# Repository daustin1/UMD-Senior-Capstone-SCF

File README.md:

# ece457SCF
Short Circuit Finder Senior Design Project

Team Lead: Matt Duncan;
Team Members: David Austin,
Mike Dugas

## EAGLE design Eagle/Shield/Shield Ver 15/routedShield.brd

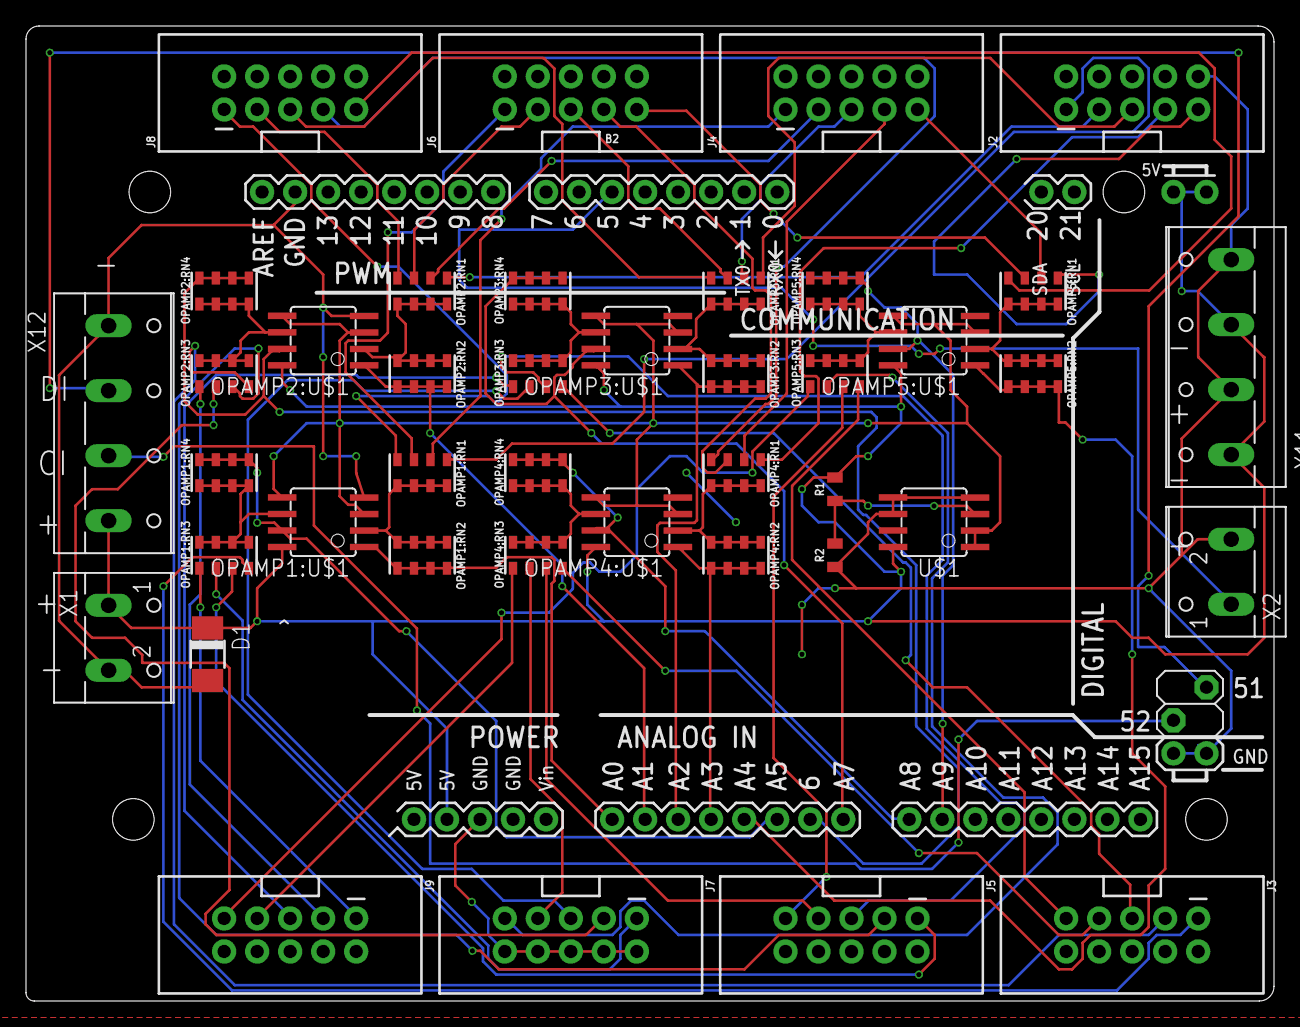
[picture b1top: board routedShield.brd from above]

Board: 2 copper layers, 96.0 x 75.0 mm, 42 parts (0 on the bottom side), 67 nets.

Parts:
B2: ARDUINO_MEGA_R3_EDITARDUINO_MEGA_EDIT; ARDUINO_MEGA_EDIT
D1: DO-214AC
J2, J3, J4, J5, J6, J7, J8, J9: AVR_SPI_PROG_5X2_NEWPTH2; 2X5-SHROUDED
OPAMP1:RN1, OPAMP1:RN2, OPAMP1:RN3, OPAMP1:RN4, OPAMP2:RN1, OPAMP2:RN2, OPAMP2:RN3, OPAMP2:RN4, OPAMP3:RN1, OPAMP3:RN2, OPAMP3:RN3, OPAMP3:RN4, OPAMP4:RN1, OPAMP4:RN2, OPAMP4:RN3, OPAMP4:RN4, OPAMP5:RN1, OPAMP5:RN2, OPAMP5:RN3, OPAMP5:RN4: 10k; 0805-ARV_EDIT10K
OPAMP1:U$1, OPAMP2:U$1, OPAMP3:U$1, OPAMP4:U$1, OPAMP5:U$1: MCP6002SMT; SOIC8
R1, R2: 1k; 0805
U$1: MCP6002SMT; SOIC8
X1, X2: W237-102
X11, X12: W237-4

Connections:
+5V: B2.5V@0, B2.5V@1, B2.5V@2, D1.C, OPAMP1:U$1.8, OPAMP2:U$1.8, OPAMP3:U$1.8, OPAMP4:U$1.8, OPAMP5:U$1.8, R1.2, U$1.8, X1.1, X11.1, X11.3, X12.4
A1O: B2.A0, OPAMP1:RN2.5, OPAMP1:RN2.6, OPAMP1:RN2.7, OPAMP1:RN2.8, OPAMP1:U$1.1
A2O: B2.A1, OPAMP2:RN2.5, OPAMP2:RN2.6, OPAMP2:RN2.7, OPAMP2:RN2.8, OPAMP2:U$1.1
A3O: B2.A2, OPAMP3:RN2.5, OPAMP3:RN2.6, OPAMP3:RN2.7, OPAMP3:RN2.8, OPAMP3:U$1.1
A4O: B2.A3, OPAMP4:RN2.5, OPAMP4:RN2.6, OPAMP4:RN2.7, OPAMP4:RN2.8, OPAMP4:U$1.1
A5O: B2.A4, OPAMP5:RN2.5, OPAMP5:RN2.6, OPAMP5:RN2.7, OPAMP5:RN2.8, OPAMP5:U$1.1
A6O: B2.A5, OPAMP1:RN4.5, OPAMP1:RN4.6, OPAMP1:RN4.7, OPAMP1:RN4.8, OPAMP1:U$1.7
A7O: B2.A6, OPAMP2:RN4.5, OPAMP2:RN4.6, OPAMP2:RN4.7, OPAMP2:RN4.8, OPAMP2:U$1.7
A8O: B2.A7, OPAMP3:RN4.5, OPAMP3:RN4.6, OPAMP3:RN4.7, OPAMP3:RN4.8, OPAMP3:U$1.7
A9O: B2.A8, OPAMP4:RN4.5, OPAMP4:RN4.6, OPAMP4:RN4.7, OPAMP4:RN4.8, OPAMP4:U$1.7
A10O: B2.A9, OPAMP5:RN4.5, OPAMP5:RN4.6, OPAMP5:RN4.7, OPAMP5:RN4.8, OPAMP5:U$1.7
CI: B2.52, X12.3
DI: B2.51, X12.2
GND: B2.GND@0, B2.GND@1, B2.GND@2, B2.GND@3, B2.GND@4, D1.A, J2.2, J2.4, J2.6, J2.8, J2.10, J3.2, J3.4, J3.6, J3.8, J3.10, J4.2, J4.4, J4.6, J4.8, J4.10, J5.2, J5.4, J5.6, J5.8, J5.10, J6.2, J6.4, J6.6, J6.8, J6.10, J7.2, J7.4, J7.6, J7.8, J7.10, J8.2, J8.4, J8.6, J8.8, J8.10, J9.2, J9.4, J9.6, J9.8, J9.10, OPAMP1:U$1.4, OPAMP2:U$1.4, OPAMP3:U$1.4, OPAMP4:U$1.4, OPAMP5:U$1.4, R2.1, U$1.4, U$1.5, U$1.6, X1.2, X2.2, X11.2, X11.4, X12.1
unnamed: R1.1, R2.2, U$1.3
OPAMP1:N$1: OPAMP1:RN3.5, OPAMP1:RN3.6, OPAMP1:RN3.7, OPAMP1:RN3.8, OPAMP1:RN4.1, OPAMP1:RN4.2, OPAMP1:RN4.3, OPAMP1:RN4.4, OPAMP1:U$1.6
OPAMP1:N$2: OPAMP1:RN1.5, OPAMP1:RN1.6, OPAMP1:RN1.7, OPAMP1:RN1.8, OPAMP1:RN2.1, OPAMP1:RN2.2, OPAMP1:RN2.3, OPAMP1:RN2.4, OPAMP1:U$1.2
OPAMP2:N$1: OPAMP2:RN3.5, OPAMP2:RN3.6, OPAMP2:RN3.7, OPAMP2:RN3.8, OPAMP2:RN4.1, OPAMP2:RN4.2, OPAMP2:RN4.3, OPAMP2:RN4.4, OPAMP2:U$1.6
OPAMP2:N$2: OPAMP2:RN1.5, OPAMP2:RN1.6, OPAMP2:RN1.7, OPAMP2:RN1.8, OPAMP2:RN2.1, OPAMP2:RN2.2, OPAMP2:RN2.3, OPAMP2:RN2.4, OPAMP2:U$1.2
OPAMP3:N$1: OPAMP3:RN3.5, OPAMP3:RN3.6, OPAMP3:RN3.7, OPAMP3:RN3.8, OPAMP3:RN4.1, OPAMP3:RN4.2, OPAMP3:RN4.3, OPAMP3:RN4.4, OPAMP3:U$1.6
OPAMP3:N$2: OPAMP3:RN1.5, OPAMP3:RN1.6, OPAMP3:RN1.7, OPAMP3:RN1.8, OPAMP3:RN2.1, OPAMP3:RN2.2, OPAMP3:RN2.3, OPAMP3:RN2.4, OPAMP3:U$1.2
OPAMP4:N$1: OPAMP4:RN3.5, OPAMP4:RN3.6, OPAMP4:RN3.7, OPAMP4:RN3.8, OPAMP4:RN4.1, OPAMP4:RN4.2, OPAMP4:RN4.3, OPAMP4:RN4.4, OPAMP4:U$1.6
OPAMP4:N$2: OPAMP4:RN1.5, OPAMP4:RN1.6, OPAMP4:RN1.7, OPAMP4:RN1.8, OPAMP4:RN2.1, OPAMP4:RN2.2, OPAMP4:RN2.3, OPAMP4:RN2.4, OPAMP4:U$1.2
OPAMP5:N$1: OPAMP5:RN3.5, OPAMP5:RN3.6, OPAMP5:RN3.7, OPAMP5:RN3.8, OPAMP5:RN4.1, OPAMP5:RN4.2, OPAMP5:RN4.3, OPAMP5:RN4.4, OPAMP5:U$1.6
OPAMP5:N$2: OPAMP5:RN1.5, OPAMP5:RN1.6, OPAMP5:RN1.7, OPAMP5:RN1.8, OPAMP5:RN2.1, OPAMP5:RN2.2, OPAMP5:RN2.3, OPAMP5:RN2.4, OPAMP5:U$1.2
S1A: J2.1, OPAMP1:RN1.1
S1B: J3.1, OPAMP1:RN3.4
S2A: J2.3, OPAMP2:RN1.1
S2B: J3.3, OPAMP2:RN3.4
S3A: J2.5, OPAMP3:RN1.1
S3B: J3.5, OPAMP3:RN3.4
S4A: J2.7, OPAMP4:RN1.1
S4B: J3.7, OPAMP4:RN3.4
S5A: J2.9, OPAMP5:RN1.1
S5B: J3.9, OPAMP5:RN3.4
S6A: J4.1, OPAMP1:RN1.2
S6B: J5.1, OPAMP1:RN3.3
S7A: J4.3, OPAMP2:RN1.2
S7B: J5.3, OPAMP2:RN3.3
S8A: J4.5, OPAMP3:RN1.2
S8B: J5.5, OPAMP3:RN3.3
S9A: J4.7, OPAMP4:RN1.2
S9B: J5.7, OPAMP4:RN3.3
S10A: J4.9, OPAMP5:RN1.2
S10B: J5.9, OPAMP5:RN3.3
S11A: J6.1, OPAMP1:RN1.3
S11B: J7.1, OPAMP1:RN3.2
S12A: J6.3, OPAMP2:RN1.3
S12B: J7.3, OPAMP2:RN3.2
S13A: J6.5, OPAMP3:RN1.3
S13B: J7.5, OPAMP3:RN3.2
S14A: J6.7, OPAMP4:RN1.3
S14B: J7.7, OPAMP4:RN3.2
S15A: J6.9, OPAMP5:RN1.3
S15B: J7.9, OPAMP5:RN3.2
S16A: J8.1, OPAMP1:RN1.4
S16B: J9.1, OPAMP1:RN3.1
S17A: J8.3, OPAMP2:RN1.4
S17B: J9.3, OPAMP2:RN3.1
S18A: J8.5, OPAMP3:RN1.4
S18B: J9.5, OPAMP3:RN3.1
S19A: J8.7, OPAMP4:RN1.4
S19B: J9.7, OPAMP4:RN3.1
S20A: J8.9, OPAMP5:RN1.4
S20B: J9.9, OPAMP5:RN3.1
TTL: B2.5, X2.1
VREF: OPAMP1:U$1.3, OPAMP1:U$1.5, OPAMP2:U$1.3, OPAMP2:U$1.5, OPAMP3:U$1.3, OPAMP3:U$1.5, OPAMP4:U$1.3, OPAMP4:U$1.5, OPAMP5:U$1.3, OPAMP5:U$1.5, U$1.1, U$1.2

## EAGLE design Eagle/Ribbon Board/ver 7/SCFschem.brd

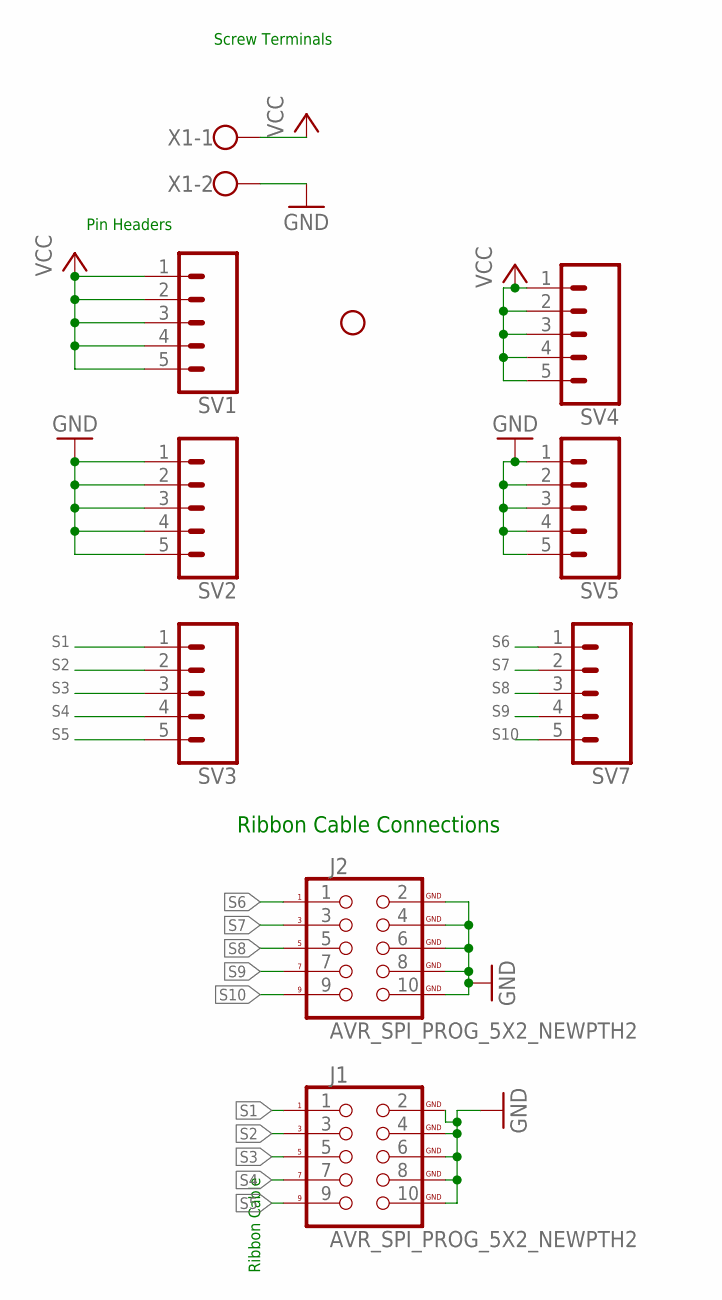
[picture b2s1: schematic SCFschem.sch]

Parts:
H1: STAND-OFF
J1, J2: AVR_SPI_PROG_5X2_NEWPTH2; 2X5-SHROUDED
SV1, SV2, SV3, SV4, SV5, SV7: CONN_05; 1X05
X1: 1X02_5MM_SCREW; W237-102

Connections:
GND: J1.2 (GND), J1.4 (GND), J1.6 (GND), J1.8 (GND), J1.10 (GND), J2.2 (GND), J2.4 (GND), J2.6 (GND), J2.8 (GND), J2.10 (GND), SV2.1, SV2.2, SV2.3, SV2.4, SV2.5, SV5.1, SV5.2, SV5.3, SV5.4, SV5.5, X1.2
S1: J1.1, SV3.1
S2: J1.3, SV3.2
S3: J1.5, SV3.3
S4: J1.7, SV3.4
S5: J1.9, SV3.5
S6: J2.1, SV7.1
S7: J2.3, SV7.2
S8: J2.5, SV7.3
S9: J2.7, SV7.4
S10: J2.9, SV7.5
VCC: SV1.1, SV1.2, SV1.3, SV1.4, SV1.5, SV4.1, SV4.2, SV4.3, SV4.4, SV4.5, X1.1

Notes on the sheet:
Screw Terminals
Ribbon Cable
Pin Headers
Ribbon Cable Connections

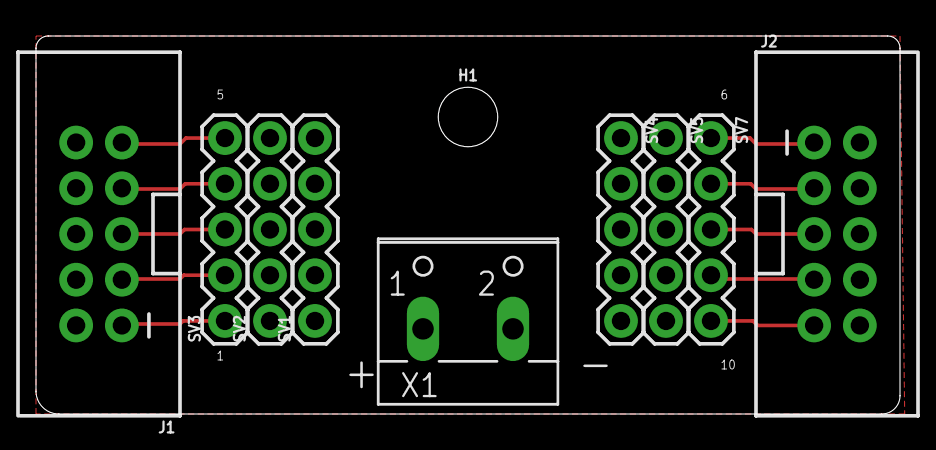
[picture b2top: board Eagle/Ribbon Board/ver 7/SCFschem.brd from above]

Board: 2 copper layers, 48.0 x 21.0 mm, 10 parts (0 on the bottom side), 12 nets.

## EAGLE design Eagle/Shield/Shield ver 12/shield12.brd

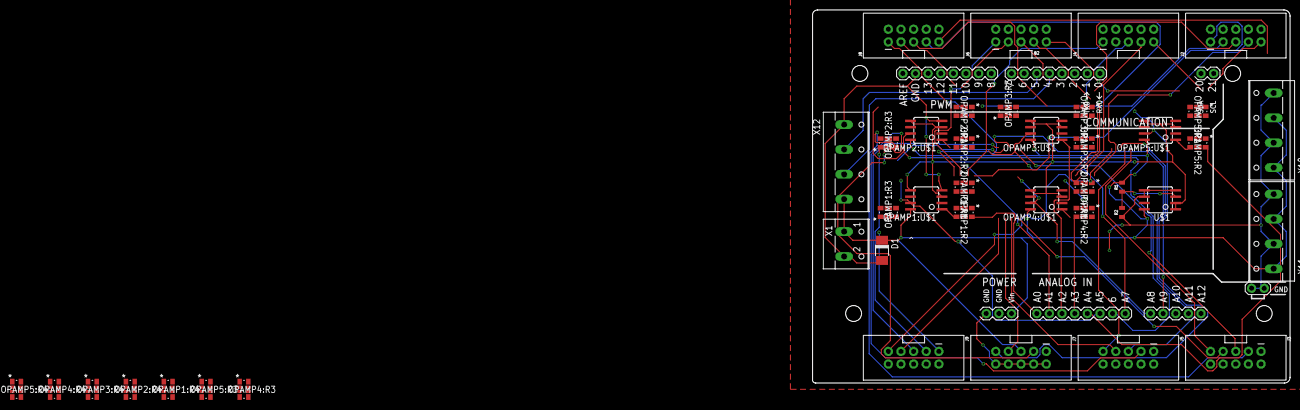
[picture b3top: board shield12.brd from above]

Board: 2 copper layers, 96.0 x 75.0 mm, 42 parts (0 on the bottom side), 46 nets.

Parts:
B2: ARDUINO_MEGA_R3_EDIT; ARDUINO_MEGA_EDIT
D1: DO-214AC
J2, J3, J4, J5, J6, J7, J8, J9: AVR_SPI_PROG_5X2_NEWPTH2; 2X5-SHROUDED
OPAMP1:R1, OPAMP1:R2, OPAMP1:R3, OPAMP1:R4, OPAMP2:R1, OPAMP2:R2, OPAMP2:R3, OPAMP2:R4, OPAMP3:R1, OPAMP3:R2, OPAMP3:R3, OPAMP3:R4, OPAMP4:R1, OPAMP4:R2, OPAMP4:R3, OPAMP4:R4, OPAMP5:R1, OPAMP5:R2, OPAMP5:R3, OPAMP5:R4: YC164-JR-0710KL; YAG_YC164
OPAMP1:U$1, OPAMP2:U$1, OPAMP3:U$1, OPAMP4:U$1, OPAMP5:U$1: MCP6002SMT; SOIC8
R1, R2: 1k; 0805
U$1: MCP6002SMT; SOIC8
X1: W237-102
X10, X11, X12: W237-4

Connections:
+5V: B2.VIN, D1.C, OPAMP1:U$1.8, OPAMP2:U$1.8, OPAMP3:U$1.8, OPAMP4:U$1.8, OPAMP5:U$1.8, R1.2, U$1.8, X1.1, X10.1, X10.3, X11.1, X11.3, X12.4
A1O: B2.A0, OPAMP1:R2.5, OPAMP1:R2.6, OPAMP1:R2.7, OPAMP1:R2.8, OPAMP1:U$1.1
A2O: B2.A1, OPAMP2:R2.5, OPAMP2:R2.6, OPAMP2:R2.7, OPAMP2:R2.8, OPAMP2:U$1.1
A3O: B2.A2, OPAMP3:R2.5, OPAMP3:R2.6, OPAMP3:R2.7, OPAMP3:R2.8, OPAMP3:U$1.1
A4O: B2.A3, OPAMP4:R2.5, OPAMP4:R2.6, OPAMP4:R2.7, OPAMP4:R2.8, OPAMP4:U$1.1
A5O: B2.A4, OPAMP5:R2.5, OPAMP5:R2.6, OPAMP5:R2.7, OPAMP5:R2.8, OPAMP5:U$1.1
A6O: B2.A5, OPAMP1:R4.5, OPAMP1:R4.6, OPAMP1:R4.7, OPAMP1:R4.8, OPAMP1:U$1.7
A7O: B2.A6, OPAMP2:R4.5, OPAMP2:R4.6, OPAMP2:R4.7, OPAMP2:R4.8, OPAMP2:U$1.7
A8O: B2.A7, OPAMP3:R4.5, OPAMP3:R4.6, OPAMP3:R4.7, OPAMP3:R4.8, OPAMP3:U$1.7
A9O: B2.A8, OPAMP4:R4.5, OPAMP4:R4.6, OPAMP4:R4.7, OPAMP4:R4.8, OPAMP4:U$1.7
A10O: B2.A9, OPAMP5:R4.5, OPAMP5:R4.6, OPAMP5:R4.7, OPAMP5:R4.8, OPAMP5:U$1.7
CI: B2.4, X12.3
DI: B2.5, X12.2
GND: B2.GND@0, B2.GND@1, B2.GND@2, B2.GND@3, B2.GND@4, D1.A, J2.2, J2.4, J2.6, J2.8, J2.10, J3.2, J3.4, J3.6, J3.8, J3.10, J4.2, J4.4, J4.6, J4.8, J4.10, J5.2, J5.4, J5.6, J5.8, J5.10, J6.2, J6.4, J6.6, J6.8, J6.10, J7.2, J7.4, J7.6, J7.8, J7.10, J8.2, J8.4, J8.6, J8.8, J8.10, J9.2, J9.4, J9.6, J9.8, J9.10, OPAMP1:U$1.4, OPAMP2:U$1.4, OPAMP3:U$1.4, OPAMP4:U$1.4, OPAMP5:U$1.4, R2.1, U$1.4, U$1.5, U$1.6, X1.2, X10.2, X10.4, X11.2, X11.4, X12.1
unnamed: R1.1, R2.2, U$1.3
OPAMP1:N$1: OPAMP1:R3.5, OPAMP1:R3.6, OPAMP1:R3.7, OPAMP1:R3.8, OPAMP1:R4.1, OPAMP1:R4.2, OPAMP1:R4.3, OPAMP1:R4.4, OPAMP1:U$1.6
OPAMP1:N$2: OPAMP1:R1.5, OPAMP1:R1.6, OPAMP1:R1.7, OPAMP1:R1.8, OPAMP1:R2.1, OPAMP1:R2.2, OPAMP1:R2.3, OPAMP1:R2.4, OPAMP1:U$1.2
OPAMP2:N$1: OPAMP2:R3.5, OPAMP2:R3.6, OPAMP2:R3.7, OPAMP2:R3.8, OPAMP2:R4.1, OPAMP2:R4.2, OPAMP2:R4.3, OPAMP2:R4.4, OPAMP2:U$1.6
OPAMP2:N$2: OPAMP2:R1.5, OPAMP2:R1.6, OPAMP2:R1.7, OPAMP2:R1.8, OPAMP2:R2.1, OPAMP2:R2.2, OPAMP2:R2.3, OPAMP2:R2.4, OPAMP2:U$1.2
OPAMP3:N$1: OPAMP3:R3.5, OPAMP3:R3.6, OPAMP3:R3.7, OPAMP3:R3.8, OPAMP3:R4.1, OPAMP3:R4.2, OPAMP3:R4.3, OPAMP3:R4.4, OPAMP3:U$1.6
OPAMP3:N$2: OPAMP3:R1.5, OPAMP3:R1.6, OPAMP3:R1.7, OPAMP3:R1.8, OPAMP3:R2.1, OPAMP3:R2.2, OPAMP3:R2.3, OPAMP3:R2.4, OPAMP3:U$1.2
OPAMP4:N$1: OPAMP4:R3.5, OPAMP4:R3.6, OPAMP4:R3.7, OPAMP4:R3.8, OPAMP4:R4.1, OPAMP4:R4.2, OPAMP4:R4.3, OPAMP4:R4.4, OPAMP4:U$1.6
OPAMP4:N$2: OPAMP4:R1.5, OPAMP4:R1.6, OPAMP4:R1.7, OPAMP4:R1.8, OPAMP4:R2.1, OPAMP4:R2.2, OPAMP4:R2.3, OPAMP4:R2.4, OPAMP4:U$1.2
OPAMP5:N$1: OPAMP5:R3.5, OPAMP5:R3.6, OPAMP5:R3.7, OPAMP5:R3.8, OPAMP5:R4.1, OPAMP5:R4.2, OPAMP5:R4.3, OPAMP5:R4.4, OPAMP5:U$1.6
OPAMP5:N$2: OPAMP5:R1.5, OPAMP5:R1.6, OPAMP5:R1.7, OPAMP5:R1.8, OPAMP5:R2.1, OPAMP5:R2.2, OPAMP5:R2.3, OPAMP5:R2.4, OPAMP5:U$1.2
S1B: J3.1, OPAMP1:R3.1
S2B: J3.3, OPAMP2:R3.1
S3B: J3.5, OPAMP3:R3.1
S4B: J3.7, OPAMP4:R3.1
S5B: J3.9, OPAMP5:R3.1
S6B: J5.1, OPAMP1:R3.2
S7B: J5.3, OPAMP2:R3.2
S8B: J5.5, OPAMP3:R3.2
S9B: J5.7, OPAMP4:R3.2
S10B: J5.9, OPAMP5:R3.2
S11B: J7.1, OPAMP1:R3.3
S12B: J7.3, OPAMP2:R3.3
S13B: J7.5, OPAMP3:R3.3
S14B: J7.7, OPAMP4:R3.3
S15B: J7.9, OPAMP5:R3.3
S16B: J9.1, OPAMP1:R3.4
S17B: J9.3, OPAMP2:R3.4
S18B: J9.5, OPAMP3:R3.4
S19B: J9.7, OPAMP4:R3.4
S20B: J9.9, OPAMP5:R3.4
VREF: OPAMP1:U$1.3, OPAMP1:U$1.5, OPAMP2:U$1.3, OPAMP2:U$1.5, OPAMP3:U$1.3, OPAMP3:U$1.5, OPAMP4:U$1.3, OPAMP4:U$1.5, OPAMP5:U$1.3, OPAMP5:U$1.5, U$1.1, U$1.2

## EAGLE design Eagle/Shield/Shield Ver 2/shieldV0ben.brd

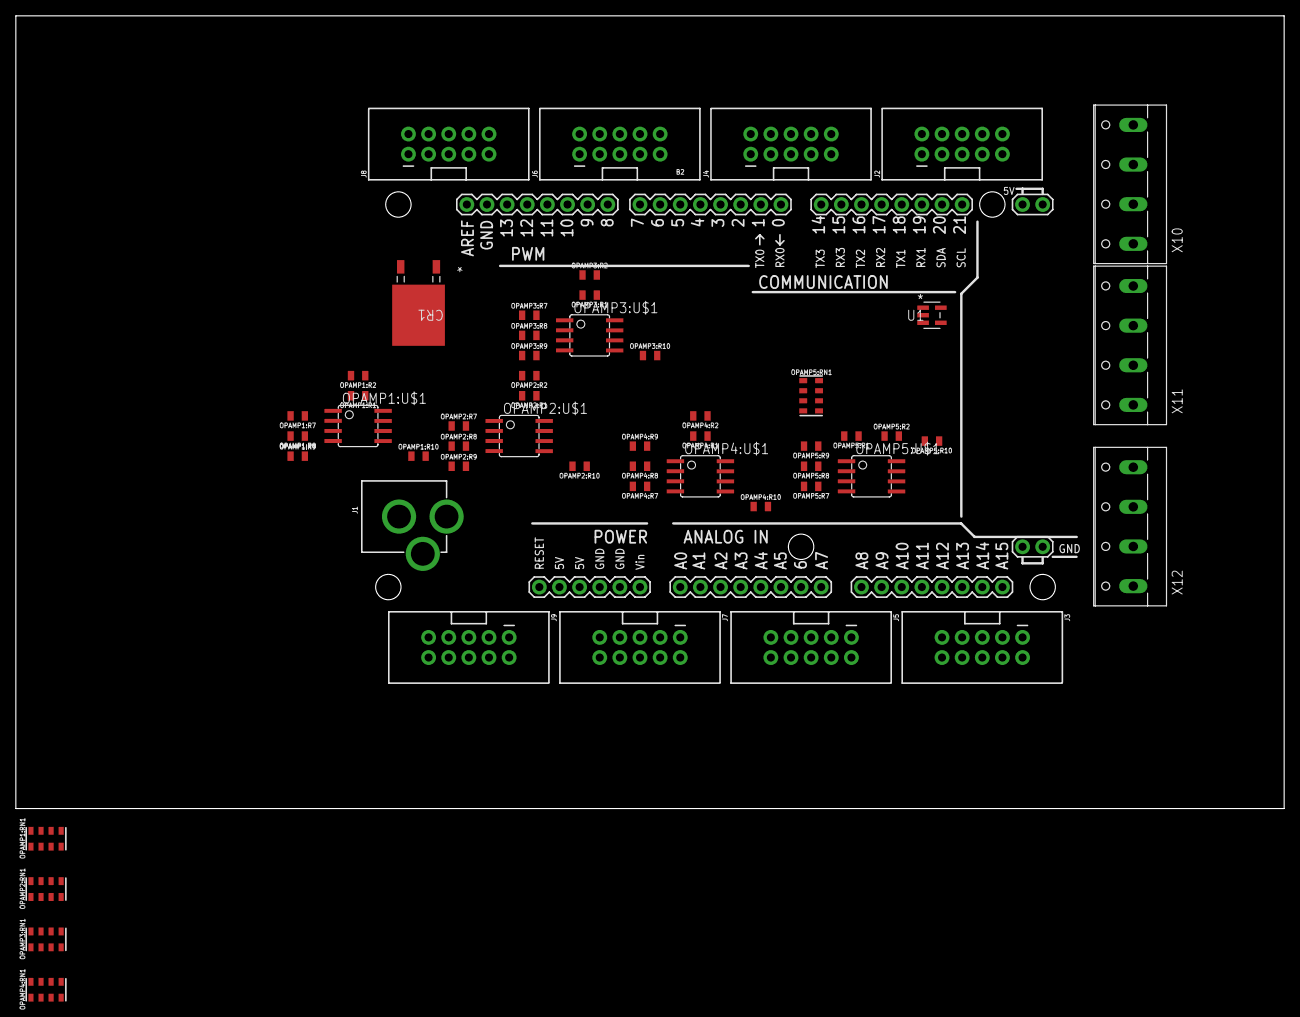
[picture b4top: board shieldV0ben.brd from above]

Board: 2 copper layers, 160.0 x 100.0 mm, 55 parts (0 on the bottom side), 62 nets, no tracks yet.

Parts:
B2: ARDUINO_MEGA_R3_EDIT; ARDUINO_MEGA_EDIT
CR1: L7805CDT-TR; DPAK
J1: POWER_JACK; POWER_JACK_PTH
J2, J3, J4, J5, J6, J7, J8, J9: AVR_SPI_PROG_5X2_NEWPTH2; 2X5-SHROUDED
OPAMP1:R1, OPAMP1:R2, OPAMP2:R1, OPAMP2:R2, OPAMP3:R1, OPAMP3:R2, OPAMP4:R1, OPAMP4:R2, OPAMP5:R1, OPAMP5:R2: 1k; 0805
OPAMP1:R7, OPAMP1:R8, OPAMP1:R9, OPAMP1:R10, OPAMP2:R7, OPAMP2:R8, OPAMP2:R9, OPAMP2:R10, OPAMP3:R7, OPAMP3:R8, OPAMP3:R9, OPAMP3:R10, OPAMP4:R7, OPAMP4:R8, OPAMP4:R9, OPAMP4:R10, OPAMP5:R7, OPAMP5:R8, OPAMP5:R9, OPAMP5:R10: 4k; 0805-4K
OPAMP1:RN1, OPAMP2:RN1, OPAMP3:RN1, OPAMP4:RN1, OPAMP5:RN1: 4k; 0805-ARV_EDIT
OPAMP1:U$1, OPAMP2:U$1, OPAMP3:U$1, OPAMP4:U$1, OPAMP5:U$1: MCP6002SMT; SOIC8
U1: TPS72101DBVT; DBV5
X10, X11, X12: W237-4

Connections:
5V: B2.VIN, CR1.2, U1.1, X10.1, X10.3, X11.1, X11.3, X12.4
A1O: B2.A0, OPAMP1:R1.2, OPAMP1:U$1.1
A2O: B2.A1, OPAMP2:R1.2, OPAMP2:U$1.1
A3O: B2.A2, OPAMP3:R1.2, OPAMP3:U$1.1
A6O: B2.A5, OPAMP1:R2.2, OPAMP1:U$1.7
A7O: B2.A6, OPAMP2:R2.2, OPAMP2:U$1.7
A8O: B2.A7, OPAMP3:R2.2, OPAMP3:U$1.7
A9O: B2.A8, OPAMP4:R2.2, OPAMP4:U$1.7
A10O: B2.A9, OPAMP5:R2.2, OPAMP5:U$1.7
CI: B2.4, X12.3
DI: B2.5, X12.2
GND: B2.GND@0, B2.GND@1, B2.GND@2, B2.GND@3, B2.GND@4, CR1.3, J1.GND, J1.GNDBREAK, J2.2, J2.4, J2.6, J2.8, J2.10, J3.2, J3.4, J3.6, J3.8, J3.10, J4.2, J4.4, J4.6, J4.8, J4.10, J5.2, J5.4, J5.6, J5.8, J5.10, J6.2, J6.4, J6.6, J6.8, J6.10, J7.2, J7.4, J7.6, J7.8, J7.10, J8.2, J8.4, J8.6, J8.8, J8.10, J9.2, J9.4, J9.6, J9.8, J9.10, OPAMP1:U$1.4, OPAMP2:U$1.4, OPAMP4:U$1.4, OPAMP5:U$1.4, U1.2, X10.2, X10.4, X11.2, X11.4, X12.1
OPAMP1:N$1: OPAMP1:R1.1, OPAMP1:RN1.5, OPAMP1:RN1.6, OPAMP1:RN1.7, OPAMP1:RN1.8, OPAMP1:U$1.2
OPAMP1:N$4: OPAMP1:R2.1, OPAMP1:R7.2, OPAMP1:R8.2, OPAMP1:R9.2, OPAMP1:R10.2, OPAMP1:U$1.6
OPAMP2:N$1: OPAMP2:R1.1, OPAMP2:RN1.5, OPAMP2:RN1.6, OPAMP2:RN1.7, OPAMP2:RN1.8, OPAMP2:U$1.2
OPAMP2:N$4: OPAMP2:R2.1, OPAMP2:R7.2, OPAMP2:R8.2, OPAMP2:R9.2, OPAMP2:R10.2, OPAMP2:U$1.6
OPAMP3:N$1: OPAMP3:R1.1, OPAMP3:RN1.5, OPAMP3:RN1.6, OPAMP3:RN1.7, OPAMP3:RN1.8, OPAMP3:U$1.2
OPAMP3:N$4: OPAMP3:R2.1, OPAMP3:R7.2, OPAMP3:R8.2, OPAMP3:R9.2, OPAMP3:R10.2, OPAMP3:U$1.6
OPAMP4:N$1: OPAMP4:R1.1, OPAMP4:RN1.5, OPAMP4:RN1.6, OPAMP4:RN1.7, OPAMP4:RN1.8, OPAMP4:U$1.2
OPAMP4:N$4: OPAMP4:R2.1, OPAMP4:R7.2, OPAMP4:R8.2, OPAMP4:R9.2, OPAMP4:R10.2, OPAMP4:U$1.6
OPAMP4:OUT: OPAMP4:R1.2, OPAMP4:U$1.1
OPAMP5:N$1: OPAMP5:R1.1, OPAMP5:RN1.5, OPAMP5:RN1.6, OPAMP5:RN1.7, OPAMP5:RN1.8, OPAMP5:U$1.2
OPAMP5:N$4: OPAMP5:R2.1, OPAMP5:R7.2, OPAMP5:R8.2, OPAMP5:R9.2, OPAMP5:R10.2, OPAMP5:U$1.6
OPAMP5:OUT: OPAMP5:R1.2, OPAMP5:U$1.1
OPAMP5:VREG: OPAMP5:U$1.3, OPAMP5:U$1.5
S1A: J2.1, OPAMP1:RN1.1
S1B: J3.1, OPAMP1:R7.1
S2A: J2.3, OPAMP2:RN1.1
S2B: J3.3, OPAMP2:R7.1
S3A: J2.5, OPAMP3:RN1.1
S3B: J3.5, OPAMP3:R7.1
S4B: J3.7, OPAMP4:R7.1
S5A: J2.9, OPAMP5:RN1.1
S5B: J3.9, OPAMP5:R7.1
S6A: J4.1, OPAMP1:RN1.2
S6B: J5.1, OPAMP1:R8.1
S7A: J4.3, OPAMP2:RN1.2
S7B: J5.3, OPAMP2:R8.1
S8A: J4.5, OPAMP3:RN1.2
S8B: J5.5, OPAMP3:R8.1
S9A: J4.7, OPAMP4:RN1.2
S9B: J5.7, OPAMP4:R8.1
S10A: J4.9, OPAMP5:RN1.2
S11B: J7.1, OPAMP1:R9.1
S12A: J6.3, OPAMP2:RN1.3
S12B: J7.3, OPAMP2:R9.1
S13A: J6.5, OPAMP3:RN1.3
S13B: J7.5, OPAMP3:R9.1
S14A: J6.7, OPAMP4:RN1.3
S14B: J7.7, OPAMP4:R9.1
S15B: J7.9, OPAMP5:R9.1
S16A: J8.1, OPAMP1:RN1.4
S16B: J9.1, OPAMP1:R10.1
S17A: J8.3, OPAMP2:RN1.4
S17B: J9.3, OPAMP2:R10.1
S18A: J8.5, OPAMP3:RN1.4
S19A: J8.7, OPAMP4:RN1.4
S19B: J9.7, OPAMP4:R10.1
S20A: J8.9, OPAMP5:RN1.4
S20B: J9.9, OPAMP5:R10.1
VCC: CR1.1, J1.PWR, OPAMP1:U$1.8, OPAMP2:U$1.8, OPAMP3:U$1.8, OPAMP4:U$1.8, OPAMP5:U$1.8, U1.3
VREG: OPAMP1:U$1.3, OPAMP1:U$1.5, OPAMP2:U$1.3, OPAMP2:U$1.5, OPAMP3:U$1.3, OPAMP3:U$1.5, OPAMP4:U$1.3, OPAMP4:U$1.5, U1.5

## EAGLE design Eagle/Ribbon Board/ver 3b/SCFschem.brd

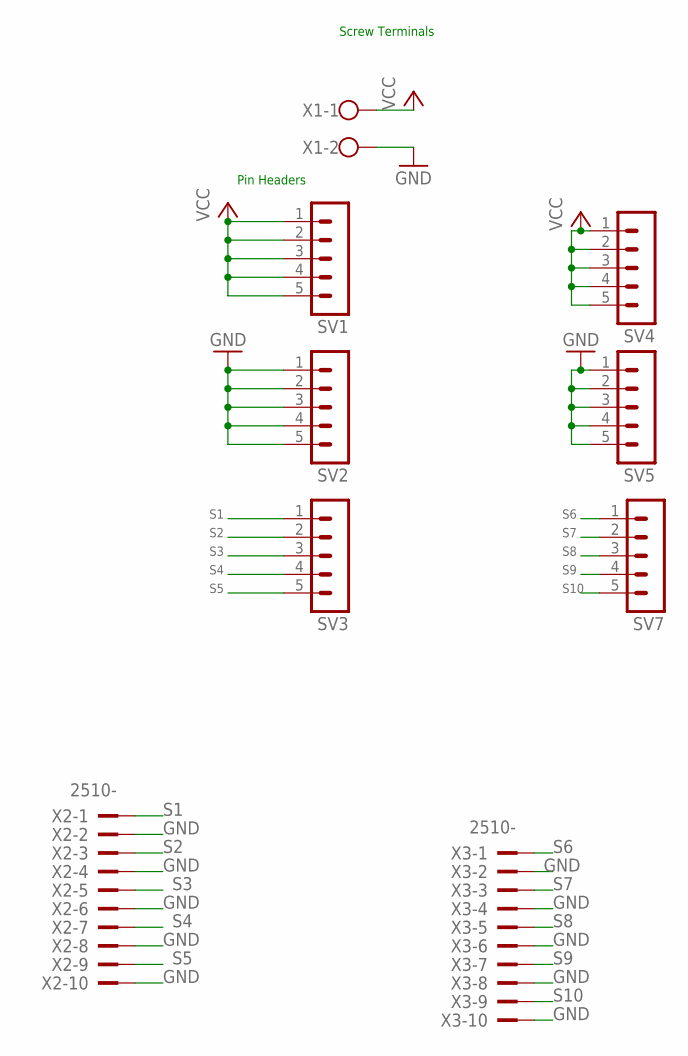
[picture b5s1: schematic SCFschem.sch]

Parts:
SV1, SV2, SV3, SV4, SV5, SV7: MA05-1
X1: 1X02_5MM_SCREW; W237-102
X2, X3: 2510-; PAK100/2500-10

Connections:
GND: SV2.1, SV2.2, SV2.3, SV2.4, SV2.5, SV5.1, SV5.2, SV5.3, SV5.4, SV5.5, X1.2, X2.2, X2.4, X2.6, X2.8, X2.10, X3.2, X3.4, X3.6, X3.8, X3.10
S1: SV3.1, X2.1
S2: SV3.2, X2.3
S3: SV3.3, X2.5
S4: SV3.4, X2.7
S5: SV3.5, X2.9
S6: SV7.1, X3.1
S7: SV7.2, X3.3
S8: SV7.3, X3.5
S9: SV7.4, X3.7
S10: SV7.5, X3.9
VCC: SV1.1, SV1.2, SV1.3, SV1.4, SV1.5, SV4.1, SV4.2, SV4.3, SV4.4, SV4.5, X1.1

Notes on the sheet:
Screw Terminals
Pin Headers

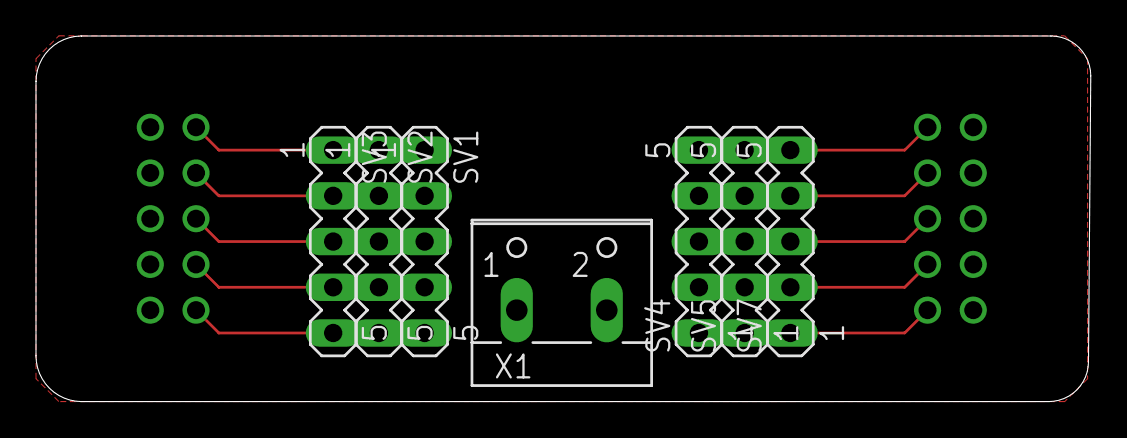
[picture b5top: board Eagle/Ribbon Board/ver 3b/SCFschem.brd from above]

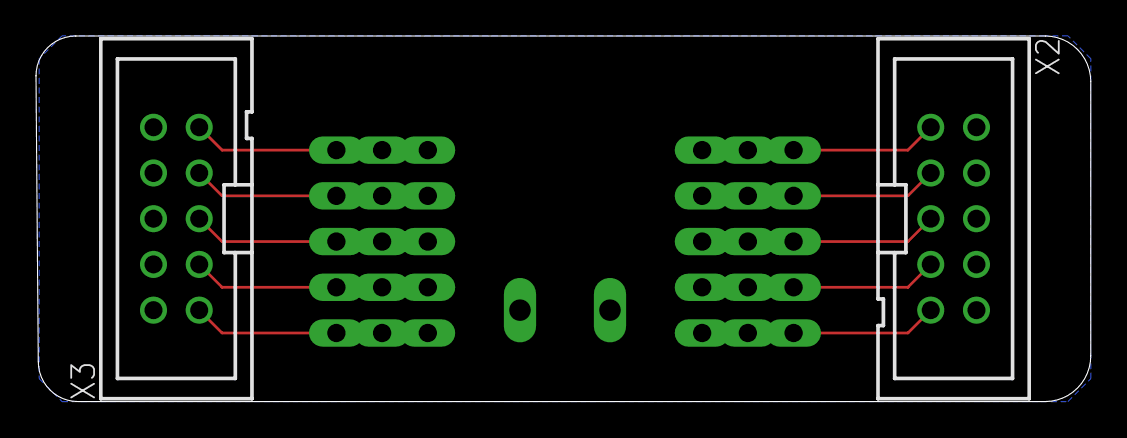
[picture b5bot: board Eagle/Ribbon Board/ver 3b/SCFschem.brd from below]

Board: 2 copper layers, 58.6 x 20.3 mm, 9 parts (2 on the bottom side), 12 nets.

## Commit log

2017-10-06 Update LICENSE
2017-11-01 Oct 11 2017 LED and Sensor Read
2017-11-01 Create Oct 11 2017 LED and Sensor Read
2017-11-01 Create MultiSim
2017-11-01 Create 12
2017-11-01 Averaging & Summing Circuits
2017-11-01 Function to control portion LEDS added
2017-11-01 Rename Oct 11 2017 LED and Sensor Read to Nov 1 2017 LED and Sensor Read
2017-11-02 Set theme jekyll-theme-cayman
2017-11-02 Create 123
2017-11-02 LED and Sensor Map Ver 3
    Code shortened, split into sections of the LED strip. Changed values of ADC to be used for LEDS
2017-11-02 Renamed the files to fit a versioning scheme
    Edited Summing Ver 4 to test Dr. Viall's suggestions
2017-11-09 Updated Summing Circuit
2017-11-28 Summing Two Sensors with the OP Amp Purchased
2017-11-28 Averaging Four Sensors with OP AMP
2018-02-07 File organization, progress with atmel conv
2018-02-12 Atmega2560 tested, 328P compiled and runs on ver 1
2018-02-25 Eagle files as of 2/24
2018-03-12 Updated ver 3
2018-03-13 Version 3b of dummy pcb
2018-03-20 ver 4
2018-03-26 Updated Ribbon Boards and revamped Shield
2018-03-26 Updated op-amp circuit DBM, added resistor arrays, new gerbers for ribbon board and updated drill size
2018-03-26 Reorganized files for the Eagle SKetches
2018-03-29 Multiple re-worked versions of shield, gerbers and gerbv made for current version
2018-03-29 Finalized the ribbon boards and shield with Ben's recommendations. Updated gerbers are included
2018-04-02 Re-aligned OP Amps and Resistors, and added the mating OP Amp for VREF, gerbs updated
2018-04-05 Added pins 51 and 52 to use SPI for LEDS, re ran gerbers. The code now outputs to the LEDS over SPI and edits were made so that the strip is only outputted once
2018-04-05 Added 5V pins and added labels for + and -
2018-04-06 Panelized board for oshpark
2018-04-24 Added averaging function to create ambient at beginning
2018-04-25 Added all arrays into code, and color map for each array
2018-05-01 Final versioning of code, updated rev. 2 of eagle shield board, reorganized code
2018-05-01 Added past versions of SCF_Arduino_Ver0 - 1
2018-10-15 Set theme jekyll-theme-slate

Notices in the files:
parts and their libraries:
SparkFun-Connectors: Licensing: Creative Commons ShareAlike 4.0 International - https://creativecommons.org/licenses/by-sa/4.0
